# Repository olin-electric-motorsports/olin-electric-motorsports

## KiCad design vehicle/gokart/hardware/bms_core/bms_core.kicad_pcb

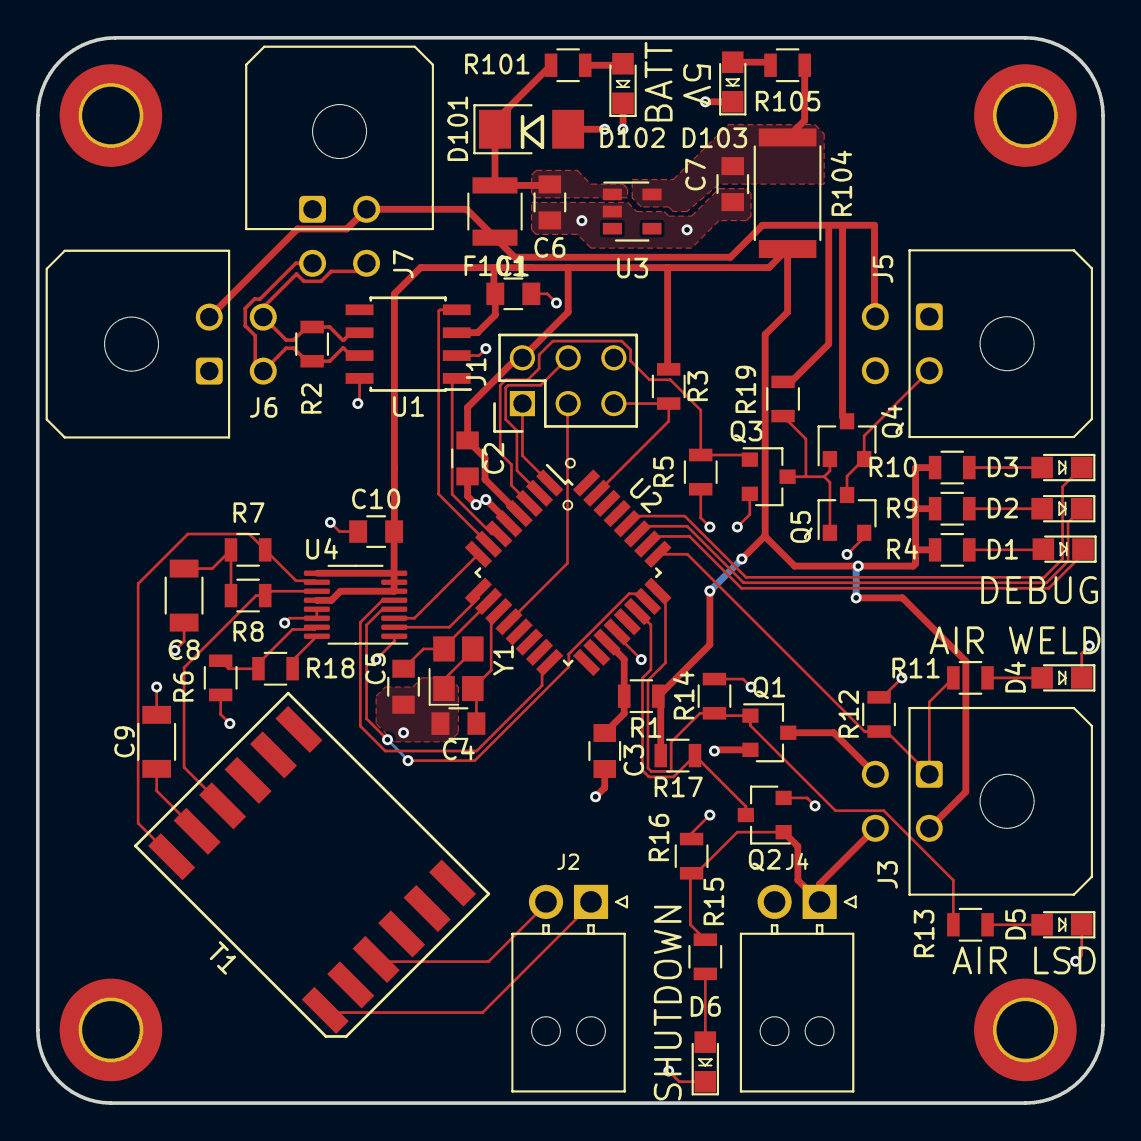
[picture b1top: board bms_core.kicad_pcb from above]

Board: 2 copper layers, 59.2 x 59.2 mm, 60 parts (0 on the bottom side), 47 nets.

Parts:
C1, C2: C_0.1uF; C_0805_OEM
C3: C_100pF; C_0805_OEM
C4, C5: C_30pF; C_0805_OEM
C6, C7, C10: C_1uF; C_0805_OEM
C8, C9: C_10nF; C_1206_OEM
D1, D2, D3, D4, D5, D6, D102, D103: LED_0805; LED_0805_OEM
D101: D_Zener_18V; DO-214AA
F101: F_500mA_16V; Fuse_1210
J1: CONN_02X03; Pin_Header_Straight_2x03
J2, J4: NanoFit_RA_TH_02; NanoFit_Molex_1x02x2.50mm_Angled_OEM
J3, J5, J6, J7: MicroFit_RA_4
Q1, Q2, Q3, Q5: SSM3K333R; SOT-23F
Q4: SSM3J334R; SOT-23F
R1: R_100; R_0805_OEM
R2: R_120_DNP; R_0805_OEM
R3, R5, R12, R14, R16, R17: R_10K; R_0805_OEM
R4, R9, R10, R11, R13, R15, R105: R_200; R_0805_OEM
R6, R18, R19, R101: R_1K; R_0805_OEM
R7, R8: R_60.4; R_0805_OEM
R104: R_0_2512; R_2512_OEM
T1: T_LAN_SM91501ALE
U1: MCP2561-E_SN; SOIC-8_3.9x4.9mm_Pitch1.27mm_OEM
U2: ATMEGA16M1; TQFP-32_7x7mm_Pitch0.8mm
U3: AP7370; SOT-23-5
U4: LTC6820HMS; MSOP-16_3x4mm_P0.5mm
Y1: Crystal_SMD; Crystal_SMD_FA238

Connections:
+5V: C1.1, C2.1, C10.1, J1.2, J3.2, R1.1, R3.1, R4.1, R9.1, R10.1, R17.2, R104.1, U1.3, U2.4, U4.6, U4.7, U4.8, U4.9, U4.12
+BATT: F101.2, J5.3, J6.2, J7.2, Q4.3, R19.1
/AIR_LSD: Q1.1, R13.1, R14.1, U2.24
/AIR_WELD: J3.1, R11.1, R12.1, U2.25
/CAN_+: J6.3, J7.3, R2.1, U1.7
/CAN_-: J6.4, J7.4, R2.2, U1.6
/CAN_RX: U1.4, U2.7
/CAN_TX: U1.1, U2.6
/COIL_+: J3.4, J4.1, Q2.1, R15.1, R16.1
/COIL_-: J3.3, Q1.3
/CS_iso: U2.16, U4.5
/DEBUG_1: D1.1, U2.26
/DEBUG_2: D2.1, U2.27
/DEBUG_3: D3.1, U2.28
/FAN_PWM: J5.2, Q4.2, Q5.3
/FAN_PWM_RAW: Q3.1, R5.1, U2.3
/MISO: J1.1, U2.1
/MISO_iso: U2.8, U4.3
/MOSI: J1.4, U2.2
/MOSI_iso: U2.9, U4.2
/RESET: J1.5, R3.2, U2.31
/SCK: J1.3, U2.12
/SCK_iso: U2.23, U4.4
/SHUTDOWN_SENSE: Q2.3, R17.1, U2.22
GND: C1.2, C2.2, C3.2, C4.2, C5.2, C6.2, C7.2, C8.2, C9.2, C10.2, D4.1, D5.1, D6.1, D101.2, D102.1, D103.1, J1.6, J4.2, J5.1, J6.1, J7.1, Q1.2, Q2.2, Q3.2, Q5.2, R5.2, R6.2, R12.2, R14.2, R16.2, U1.2, U1.8, U2.5, U2.20, U3.2, U4.1, U4.13, U4.14, Y1.2, Y1.4
unnamed: C3.1, R1.2, U2.19
unnamed: C4.1, U2.11, Y1.1
unnamed: C5.1, U2.10, Y1.3
unnamed: C6.1, D101.1, F101.1, R101.1, U3.1
unnamed: C7.1, R104.2, R105.1, U3.5
unnamed: C8.1, R7.2, R8.1
unnamed: C9.1, T1.11
unnamed: D1.2, R4.2
unnamed: D2.2, R9.2
unnamed: D3.2, R10.2
unnamed: D4.2, R11.2
unnamed: D5.2, R13.2
unnamed: D6.2, R15.2
unnamed: D102.2, R101.2
unnamed: D103.2, R105.2
unnamed: J2.1, T1.1
unnamed: J2.2, T1.3
unnamed: Q3.3, Q4.1, Q5.1, R19.2
unnamed: R7.1, T1.12, U4.10
unnamed: R8.2, T1.10, U4.11
unnamed: R18.1, U4.16
unnamed: R6.1, R18.2, U4.15

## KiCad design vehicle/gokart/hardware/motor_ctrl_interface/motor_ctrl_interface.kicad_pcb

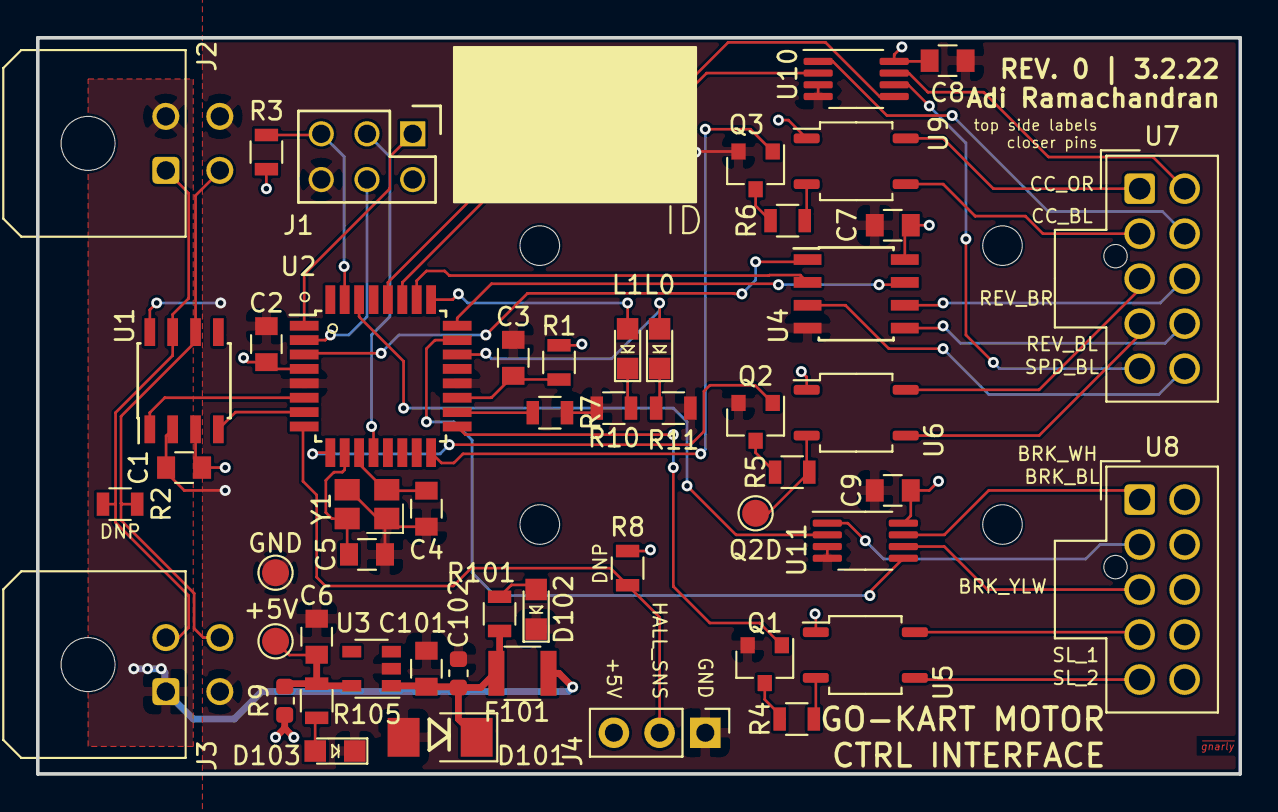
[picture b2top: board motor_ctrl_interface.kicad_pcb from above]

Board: 2 copper layers, 66.8 x 40.9 mm, 52 parts (0 on the bottom side), 55 nets.

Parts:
+5V: Test_Point_SMD; TestPoint_Pad_D1.5mm
C1, C2, C7, C8, C9, C101: C_0.1uF; C_0805_OEM
C3: C_100pF; C_0805_OEM
C4, C5: C_30pF; C_0805_OEM
C6: C_1uF; C_0805_OEM
C102: C_2.2uF; C_0603_1608Metric
D101: D_Zener_18V; DO-214AA
D102, D103: LED_0805; LED_0805_OEM
F101: F_500mA_16V; Fuse_1210
GND: Test_Point_SMD; TestPoint_Pad_D1.5mm
J1: CONN_02X03; Pin_Header_Straight_2x03
J2, J3: MicroFit_RA_4
J4: CONN_01X03; PinHeader_1x03_P2.54mm_Vertical
L0, L1: LED_0805; LED_0805_OEM
Q1, Q2, Q3: SSM3K333R; SOT-23F
Q2D: Test_Point_SMD; TestPoint_Pad_D1.5mm
R1: R_100; R_0805_OEM
R2: R_120_DNP; R_0805_OEM
R3, R7, R8: R_10K; R_0805_OEM
R4, R5, R6, R101: R_1K; R_0805_OEM
R9: R_0; R_0603_1608Metric
R10, R11: R_499; R_0805_OEM
R105: R_200; R_0805_OEM
U1: MCP2561-E_SN; SOIC-8_3.9x4.9mm_Pitch1.27mm_OEM
U2: ATMEGA16M1; TQFP-32_7x7mm_Pitch0.8mm
U3: AP7370; SOT-23-5
U4: AD5220BRZ50; SOIC-8_3.9x4.9mm_Pitch1.27mm_OEM
U5, U6, U9: CPC1004N; SOP-4_3.8x4.1mm_P2.54mm
U7, U8: NanoFit_VT_TH_10; NanoFit_VT_10
U10, U11: SN74LVC2G53; MSOP-8_3x3mm_P0.65mm
Y1: Crystal_SMD; Crystal_SMD_FA238

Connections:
+5V: C1.1, C2.1, C7.1, C8.1, C9.1, J1.2, J4.3, R1.1, R3.1, R8.1, R9.1, U1.3, U2.4, U4.8, U5.1, U6.1, U9.1, U10.8, U11.8
+BATT: F101.2, J2.2, J3.1
/BRK_A: U2.23, U11.5
/BRK_INH: U2.30, U11.2
/CAN_+: J2.1, J3.2, R2.1, U1.7
/CAN_-: J2.3, J3.4, R2.2, U1.6
/CAN_RX: U1.4, U2.7
/CAN_TX: U1.1, U2.6
/CONN_BRK_BLACK: U8.2, U11.1
/CONN_BRK_WHITE: U8.1, U11.7
/CONN_BRK_YELLOW: U8.3, U11.6
/CONN_CC_BLACK: U7.2, U9.3
/CONN_CC_ORANGE: U7.1, U9.4
/CONN_REVERSE_BLACK: U6.3, U7.4
/CONN_REVERSE_BROWN: U6.4, U7.3
/CONN_SL_1: U5.4, U8.4
/CONN_SL_2: U5.3, U8.5
/CONN_SPD_BLACK: U7.7, U10.1
/CONN_SPD_BLUE: U7.5, U10.6
/CONN_SPD_ORANGE: U7.6, U10.7
/CONN_THR_5V: U4.3, U7.10
/CONN_THR_GND: U4.6, U7.8
/CONN_THR_GREEN: U4.5, U7.9
/CRUISE_CONTROL: Q3.1, U2.16
/HALL_SNS: J4.2, R8.2, U2.8
/ID_PULLDOWN: R7.1, U2.18
/LED_0: L0.2, U2.22
/LED_1: L1.2, U2.25
/MISO: J1.1, U2.1
/MOSI: J1.4, U2.2
/POT_CLK: U2.3, U4.1
/POT_U~D: U2.26, U4.2
/POT_~CS: U2.24, U4.7
/RESET: J1.5, R3.2, U2.31
/REVERSE: Q2.1, U2.9
/SCK: J1.3, U2.12
/SL_MODE: Q1.1, U2.17
/SPD_A: U2.28, U10.5
/SPD_INH: U2.27, U10.2
GND: C1.2, C2.2, C3.2, C4.2, C5.2, C6.2, C7.2, C8.2, C9.2, C101.2, C102.2, D101.2, D102.1, D103.1, GND.1, J1.6, J2.4, J3.3, J4.1, Q1.2, Q2.2, Q3.2, R7.2, R10.2, R11.2, U1.2, U1.8, U2.5, U2.20, U3.2, U4.4, U10.3, U10.4, U11.3, U11.4, Y1.2, Y1.4
unnamed: C3.1, R1.2, U2.19
unnamed: C4.1, U2.11, Y1.1
unnamed: C5.1, U2.10, Y1.3
unnamed: +5V.1, C6.1, R9.2, R105.1, U3.5
unnamed: C101.1, C102.1, D101.1, F101.1, R101.1, U3.1
unnamed: L1.1, R10.1
unnamed: L0.1, R11.1
unnamed: D102.2, R101.2
unnamed: D103.2, R105.2
unnamed: Q1.3, R4.2
unnamed: Q2.3, R5.2
unnamed: Q3.3, R6.2
unnamed: R4.1, U5.2
unnamed: Q2D.1, R5.1, U6.2
unnamed: R6.1, U9.2

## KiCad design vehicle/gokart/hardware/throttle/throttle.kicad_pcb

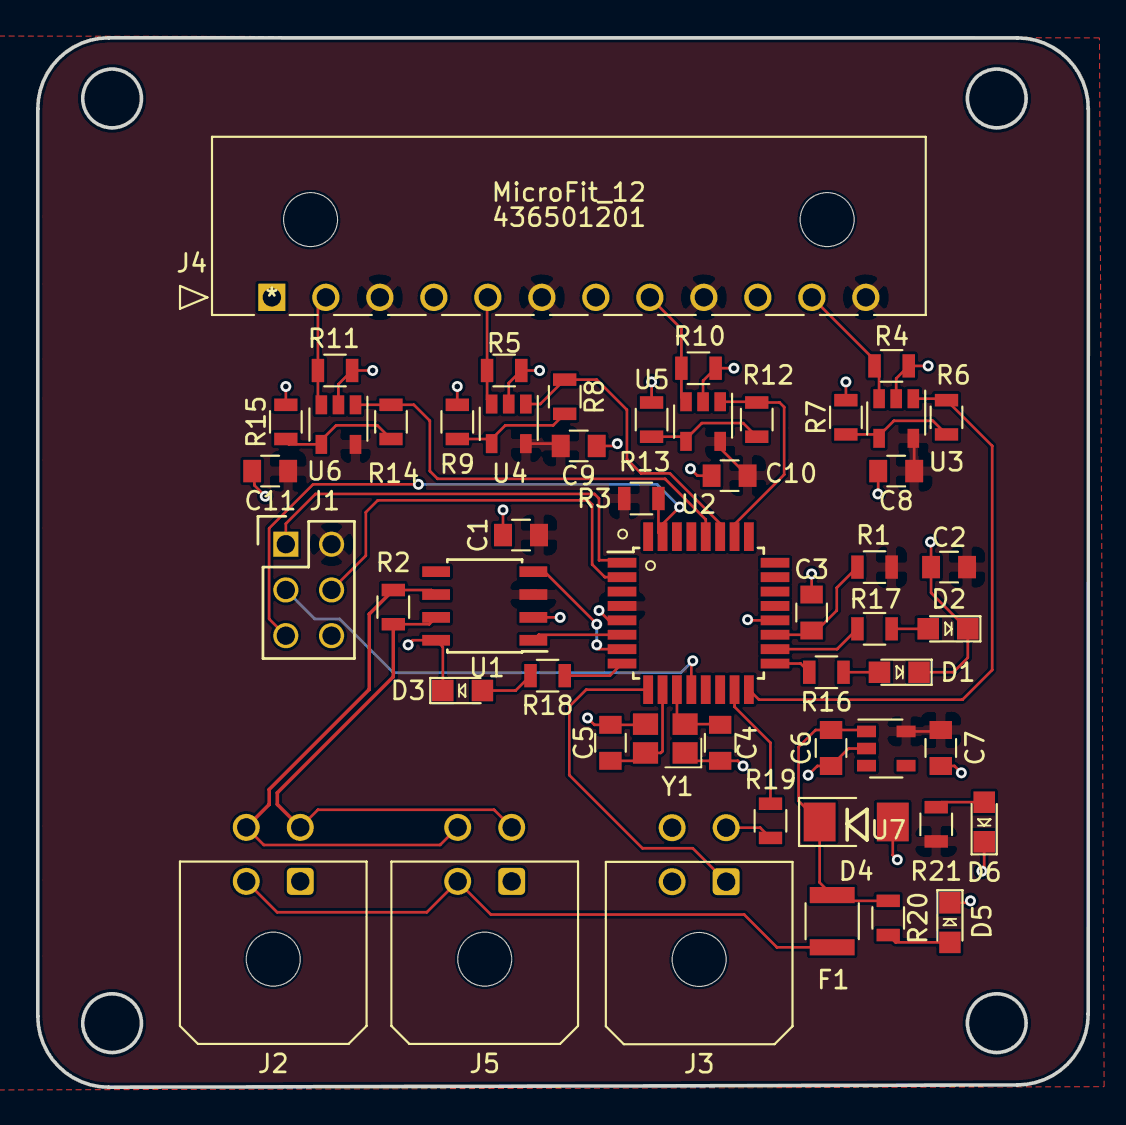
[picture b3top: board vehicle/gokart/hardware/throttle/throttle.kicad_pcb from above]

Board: 2 copper layers, 58.4 x 58.3 mm, 52 parts (0 on the bottom side), 38 nets.

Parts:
C1, C2: C_0.1uF; C_0805_OEM
C3: C_100pF; C_0805_OEM
C4, C5: C_30pF; C_0805_OEM
C6, C7, C8, C9, C10, C11: C_1uF; C_0805_OEM
D1, D5, D6: LED_0805; LED_0805_OEM
D2: LED_0805_Amber; LED_0805_OEM
D3: LED_0805_Red; LED_0805_OEM
D4: D_Zener_18V; DO-214AA
F1: F_500mA_16V; Fuse_1210
J1: CONN_02X03; Pin_Header_Straight_2x03
J2, J3, J5: MicroFit_RA_4
J4: MicroFit_12; MicroFit12_ra
R1: R_100; R_0805_OEM
R2: R_120_DNP; R_0805_OEM
R3, R6, R8, R12, R14: R_10K; R_0805_OEM
R4, R5, R10, R11: R_100K; R_0805_OEM
R7, R9, R13, R15: R_10K_DNP; R_0805_OEM
R16, R17, R18, R19, R21: R_200; R_0805_OEM
R20: R_1K; R_0805_OEM
U1: MCP2561-E_SN; SOIC-8_3.9x4.9mm_Pitch1.27mm_OEM
U2: ATMEGA16M1; TQFP-32_7x7mm_Pitch0.8mm
U3, U4, U5, U6: MCP6001; SOT-23-5_OEM
U7: AP7370; SOT-23-5
Y1: Crystal_SMD; Crystal_SMD_FA238

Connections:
+5V: C1.1, C2.1, C7.1, C8.2, C9.2, C10.2, C11.2, J1.2, J4.3, J4.6, J4.9, J4.12, R1.1, R3.1, R21.1, U1.3, U2.4, U3.5, U4.5, U5.5, U6.5, U7.5
+BATT: F1.2, J2.2, J5.2
/CAN_+: J2.3, J5.3, R2.1, U1.7
/CAN_-: J2.4, J5.4, R2.2, U1.6
/CAN_RX: U1.4, U2.7
/CAN_TX: U1.1, U2.6
/MISO: J1.1, U2.1
/MOSI: J1.4, U2.2
/PROGRAMMINGLED1: R16.1, U2.17
/PROGRAMMINGLED2: R17.1, U2.18
/PROGRAMMINGLED3: R18.1, U2.8
/READY_TO_DRIVE_LED: R19.1, U2.15
/RESET: J1.5, R3.2, U2.31
/SCK: J1.3, U2.12
/START_BUTTON: J3.1, U2.9
/VIN1: J4.11, R4.2, U3.3
/VIN2: J4.8, R10.2, U5.3
/VIN3: J4.5, R5.2, U4.3
/VIN4: J4.2, R11.2, U6.3
/VOUT1: R6.1, U2.16, U3.1
/VOUT2: R12.1, U2.26, U5.1
/VOUT3: R8.1, U2.27, U4.1
/VOUT4: R14.1, U2.28, U6.1
GND: C1.2, C2.2, C3.2, C4.2, C5.2, C6.2, C7.2, C8.1, C9.1, C10.1, C11.1, D1.1, D2.1, D3.1, D4.2, D5.1, D6.1, J1.6, J2.1, J3.2, J3.4, J4.1, J4.4, J4.7, J4.10, J5.1, R4.1, R5.1, R7.2, R9.2, R10.1, R11.1, R13.2, R15.2, U1.2, U1.8, U2.5, U2.20, U3.2, U4.2, U5.2, U6.2, U7.2, Y1.2, Y1.4
unnamed: C3.1, R1.2, U2.19
unnamed: C4.1, U2.11, Y1.1
unnamed: C5.1, U2.10, Y1.3
unnamed: C6.1, D4.1, F1.1, R20.1, U7.1
unnamed: D1.2, R16.2
unnamed: D2.2, R17.2
unnamed: D3.2, R18.2
unnamed: D5.2, R20.2
unnamed: D6.2, R21.2
unnamed: J3.3, R19.2
unnamed: R6.2, R7.1, U3.4
unnamed: R8.2, R9.1, U4.4
unnamed: R12.2, R13.1, U5.4
unnamed: R14.2, R15.1, U6.4

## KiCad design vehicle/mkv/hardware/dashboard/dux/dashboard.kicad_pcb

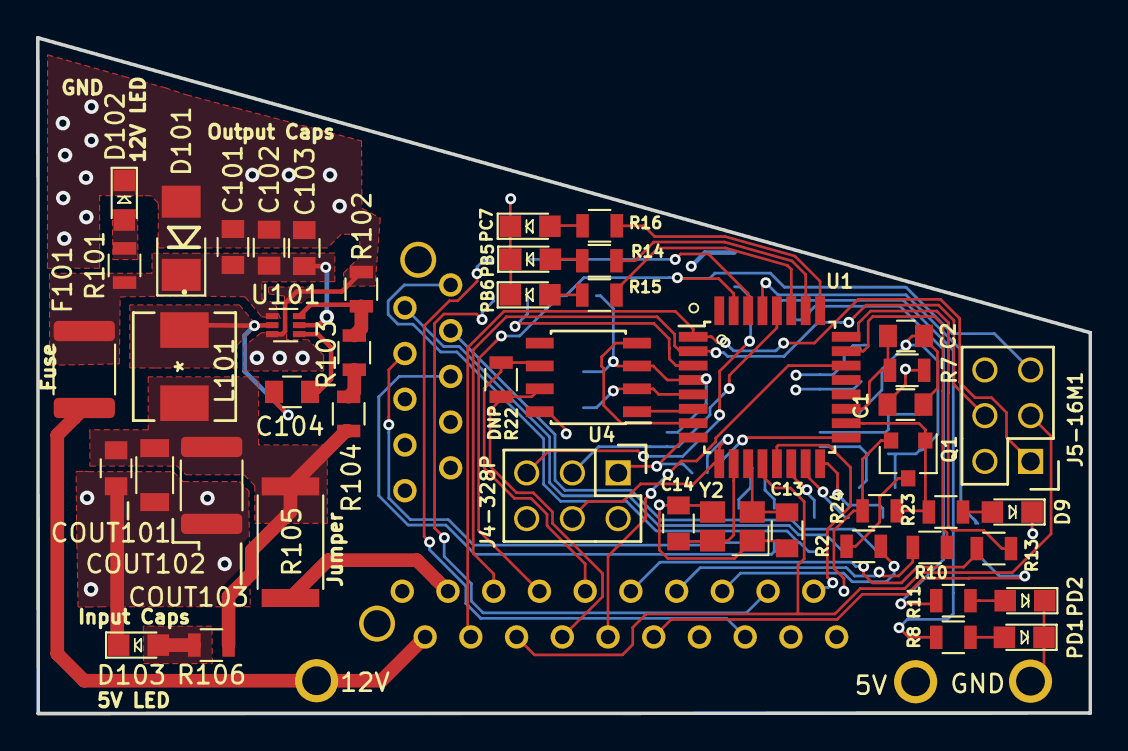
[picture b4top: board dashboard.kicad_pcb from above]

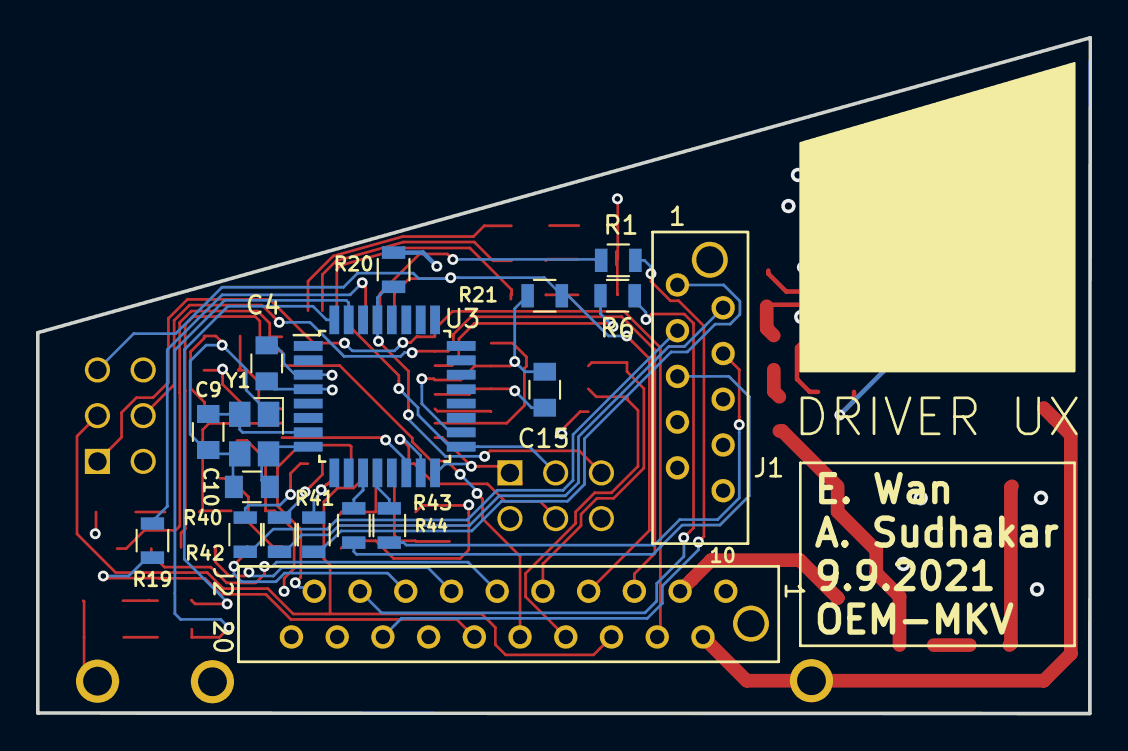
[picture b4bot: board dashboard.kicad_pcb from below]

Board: 4 copper layers, 58.5 x 37.5 mm, 68 parts (18 on the bottom side), 65 nets.

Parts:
C1, C4, C15, C101, C104: C_0.1uF; C_0805_OEM
C2: C_100pF; C_0805_OEM
C9, C10, C13, C14: C_30pF; C_0805_OEM
C102, C103: C_10uF_25V; C_0805_OEM
COUT101: C_10uF; C_0805_OEM
COUT102: C_22uF; C_1206_OEM
COUT103: C_33uF; C_1812_4532Metric
D3, D4, D5, D6, D8, D9: LED; LED_0805_OEM
D101: D_Zener_18V; DO-214AA
D102, D103: LED_0805; LED_0805_OEM
F101: F_2.6A_16V; Fuse_1812_4532Metric
J1: MM_F_VT_10; micromatch_female_vert_10
J2: MM_F_VT_20; micromatch_female_vert_20
J4-328P, J5-16M1: CONN_02X03; Pin_Header_Straight_2x03
L101: L_4.7uH; IHLP2020BZER4R7M11-L_4.7_3.2A
Q1: SSM3K333R; SOT-23F
R1, R6, R8, R10, R11, R13, R14, R15, R16, R19, R23, R40, R41, R42, R106: R_200; R_0805_OEM
R2, R7: R_100; R_0805_OEM
R20, R102: R_10K; R_0805_OEM
R21: R_10k; R_0805_OEM
R22: R_120; R_0805_OEM
R24: R_100k; R_0805_OEM
R43, R44: R_475; R_0805_OEM
R101: R_1K; R_0805_OEM
R103: R_51.1K; R_0805_OEM
R104: R_22K; R_0805_OEM
R105: R_0_2512; R_2512_OEM
TP1: TP_12V; tp_1.6mm
TP3: TP_5V; tp_1.6mm
TP5: TP_GND; tp_1.6mm
U1: ATMEGA16M1; TQFP-32_7x7mm_Pitch0.8mm
U3: ATmega328P-AU; TQFP-32_7x7mm_P0.8mm
U4: CAN_Transceiver; SOIC-8_3.9x4.9mm_Pitch1.27mm_OEM
U101: TPS563231; SOT-563
Y1, Y2: Crystal_SMD; Crystal_SMD_FA238

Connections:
+5V: C1.1, C4.1, C15.1, J1.6, J2.3, J2.18, J4-328P.2, J5-16M1.2, R7.1, R20.1, R21.1, R105.1, TP3.1, U1.4, U3.4, U3.18, U4.3
+12V: F101.1, J2.2, TP1.1
/BMS_LED: J2.12, R19.2
/BRAKE_LED: J1.3, R40.1
/CANH: J2.8, R22.1, U4.7
/CANL: J2.9, R22.2, U4.6
/CS: U1.17, U3.14
/HV_LED: J1.2, R42.1
/IMD_LED: J2.13, R10.1
/LV_LED: J1.1, R41.1
/PM_MISO: J2.4, J5-16M1.1, U1.1
/PM_MOSI: J2.5, J5-16M1.4, U1.2
/PM_RESET: J2.7, J5-16M1.5, R21.2, U1.31
/PM_SCK: J2.6, J5-16M1.3, U1.12
/RJLED1: J2.16, R1.1
/RJLED2: J2.17, R6.1
/RTD_LSD: J2.15, R2.1
/RXCAN: U1.7, U4.4
/SM_MISO: J4-328P.1, U1.8, U3.16
/SM_MOSI: J4-328P.4, U1.9, U3.15
/SM_RESET: J4-328P.5, R20.2, U3.29
/SM_SCK: J4-328P.3, U1.28, U3.17
/SOC_LED_BAR: J1.5, R44.1
/SPEED_LED_BAR: J1.4, R43.1
/START_BTN: J2.10, U1.22
/START_LED: J2.11, R13.1
/STR_POT_SENSE: J2.19, U1.13
/TXCAN: U1.6, U4.1
/XTAL1: C9.1, U3.7, Y1.1
/XTAL2: C10.1, U3.8, Y1.3
GND: C1.2, C2.2, C4.2, C9.2, C10.2, C13.2, C14.2, C15.2, C101.2, C102.2, C103.2, COUT101.2, COUT102.1, COUT103.2, D3.1, D4.1, D5.1, D6.1, D8.1, D9.1, D101.2, D102.1, D103.1, J1.7, J1.8, J1.9, J1.10, J2.1, J2.14, J2.20, J4-328P.6, J5-16M1.6, Q1.2, R24.2, R102.2, TP5.1, U1.5, U3.3, U4.2, U4.8, U101.3, Y1.2, Y1.4, Y2.2, Y2.4
unnamed: C2.1, R7.2, U1.19
unnamed: C13.1, U1.11, Y2.1
unnamed: C14.1, U1.10, Y2.3
unnamed: C101.1, C102.1, C103.1, D101.1, F101.2, R101.1, U101.1, U101.5
unnamed: C104.1, L101.1, U101.2
unnamed: C104.2, U101.4
unnamed: COUT101.1, COUT102.2, COUT103.1, L101.2, R104.1, R105.2, R106.1
unnamed: D3.2, R8.1
unnamed: D4.2, R11.1
unnamed: D5.2, R14.2
unnamed: D6.2, R15.2
unnamed: D8.2, R16.2
unnamed: D9.2, R23.2
unnamed: D102.2, R101.2
unnamed: D103.2, R106.2
unnamed: Q1.1, R23.1, R24.1, U1.18
unnamed: Q1.3, R2.2
unnamed: R1.2, U1.30
unnamed: R6.2, U1.3
unnamed: R8.2, U3.31
unnamed: R10.2, U1.23
unnamed: R11.2, U3.32
unnamed: R13.2, U1.24
unnamed: R14.1, U1.26
unnamed: R15.1, U1.27
unnamed: R16.1, U1.25
unnamed: R19.1, U1.29
unnamed: R40.2, U1.16
unnamed: R41.2, U1.14
unnamed: R42.2, U1.15
unnamed: R43.2, U3.12
unnamed: R44.2, U3.11
unnamed: R102.1, R103.2, U101.6
unnamed: R103.1, R104.2

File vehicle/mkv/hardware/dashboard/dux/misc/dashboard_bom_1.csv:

Component,Description,Part,References,Value,Footprint,Quantity Per PCB,Datasheet,Package,MPN,MFN,PurchasingLink,Link,Digi-key Part Number,Purchasing Link
1,,C_0.1uF-formula,C1 C4 C15 C101 C103,C_0.1uF,C_0805_OEM,5,http://datasheets.avx.com/X7RDielectric.pdf,Value,478-3352-1-ND,DK,https://www.digikey.com/products/en?keywords=478-3352-1-ND,,,
2,,C_100pF-formula,C2,C_100pF,C_0805_OEM,1,https://katalog.we-online.de/pbs/datasheet/885012007057.pdf,Value,732-7852-1-ND,DK,https://www.digikey.com/product-detail/en/wurth-electronics-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,,,
3,,C_2.2uF-formula,C102,C_2.2uF,C_0603_1608Metric,1,http://www.yageo.com/documents/recent/UPY-GPHC_X5R_4V-to-50V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,,311-1451-1-ND,DK,https://www.digikey.com/product-detail/en/yageo/CC0603KRX5R6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,,,
4,,C_30pF-formula,C9 C10 C13 C14,C_30pF,C_0805_OEM,4,https://media.digikey.com/pdf/Data%20Sheets/Samsung%20PDFs/C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,Value,1276-1130-1-ND,DK,https://www.digikey.com/product-detail/en/samsung-electro-me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,,,
5,,C_22uF-formula,COUT101,C_22uF,C_1206_OEM,1,https://product.tdk.com/info/en/catalog/datasheets/mlcc_comm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,,445-11693-1-ND,DK,https://www.digikey.com/product-detail/en/tdk-corporation/C3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,,,
6,,C_33uF-formula,COUT102,C_33uF,C_1812_OEM,1,https://product.tdk.com/info/en/catalog/datasheets/mlcc_comm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,,445-3924-1-ND,C4532X7R1C336M250KC,https://www.digikey.com/product-detail/en/tdk-corporation/C4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,,,
7,,C_47uF-formula,COUT103,C_47uF,C_0805_OEM,1,http://www.samsungsem.com/kr/support/product-search/mlcc/__i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,,1276-6467-1-ND,DK,https://www.digikey.com/product-detail/en/samsung-electro-me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,,,
8,,D_Zener_18V-formula,D101,D_Zener_18V,DO-214AA,1,http://www.mccsemi.com/up_pdf/SMBJ5338B-SMBJ5388B(SMB).pdf,,SMBJ5355B-TPMSCT-ND,DK,https://www.digikey.com/products/en?keywords=SMBJ5355B-TPMSCT-ND,,,
9,Light emitting diode,LED,D3 D4 D5 D6 D8 D9,LED,LED_0805_OEM,6,,,,,,,,
10,,LED_0805-formula,D102 D103,LED_0805,LED_0805_OEM,2,http://www.osram-os.com/Graphics/XPic9/00078860_0.pdf,,475-1410-1-ND,DK,https://www.digikey.com/products/en?keywords=475-1410-1-ND,,,
11,,F_500mA_16V-formula,F101,F_500mA_16V,Fuse_1210,1,https://belfuse.com/resources/CircuitProtection/datasheets/0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,,507-1786-1-ND,DK,https://www.digikey.com/product-detail/en/bel-fuse-inc/0ZCH0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,,,
12,,CONN_02X03-formula,J4 J5,CONN_02X03,Pin_Header_Straight_2x03,2,http://portal.fciconnect.com/Comergent//fci/drawing/67996.pdf,Value,609-3234-ND,DK,https://www.digikey.com/product-detail/en/amphenol-fci/67997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,,,
13,,MM_F_VT_04-formula,J3,MM_F_VT_04,micromatch_female_vert_4,1,http://www.te.com/commerce/DocumentDelivery/DDEController?Ac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,,338068-4,TE,http://www.te.com/global-en/product-338068-4.html,,,
14,,MM_F_VT_10-formula,J1,MM_F_VT_10,micromatch_female_vert_10,1,http://www.te.com/commerce/DocumentDelivery/DDEController?Ac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,,1-338068-0,TE,http://www.te.com/global-en/product-1-338068-0.html,,,
15,,MM_F_VT_20-formula,J2,MM_F_VT_20,micromatch_female_vert_20,1,http://www.te.com/commerce/DocumentDelivery/DDEController?Ac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,,2-338068-0,TE,http://www.te.com/global-en/product-2-338068-0.html,,,
16,,L_100uH-formula,L101,L_100uH,L_100uH,1,https://product.tdk.com/info/en/catalog/datasheets/inductor_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,,445-15759-1-ND,Digikey,,https://www.digikey.com/product-detail/en/tdk-corporation/NL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,,
17,,SSM3K333R-formula,Q1,SSM3K333R,SOT-23F,1,https://drive.google.com/drive/folders/0B-V-iZf33Y4GNzhDQTJZanJRbVk,,SSM3K333RLFCT-ND,DK,https://www.digikey.com/product-detail/en/toshiba-semiconduc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,,,
18,,R_0_2512-formula,R104,R_0_2512,R_2512_OEM,1,http://www.te.com/commerce/DocumentDelivery/DDEController?Ac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,,A121322CT-ND,DK,https://www.digikey.com/products/en?keywords=A121322CT-ND,,,
19,,R_100-formula,R7,R_100,R_0805_OEM,1,https://www.seielect.com/Catalog/SEI-rncp.pdf,Value,RNCP0805FTD100RCT-ND,DK,https://www.digikey.com/products/en?keywords=RNCP0805FTD100RCT-ND,,,
20,,R_100K-formula,R103,R_100K,R_0805_OEM,1,https://industrial.panasonic.com/cdbs/www-data/pdf/RDA0000/A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,,P100KCCT-ND,DK,https://www.digikey.com/product-detail/en/panasonic-electron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,,,
21,Resistor,R,R24,R_100k,R_0805_OEM,1,~,,,,,,,
22,,R_10K-formula,R20 R21,R_10K,R_0805_OEM,2,http://www.bourns.com/data/global/pdfs/CRS.pdf,Value,CRS0805-FX-1002ELFCT-ND,DK,https://www.digikey.com/products/en?keywords=CRS0805-FX-1002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,,,
23,,R_200-formula,R22,R_120,R_0805_OEM,1,https://www.seielect.com/Catalog/SEI-RMCF_RMCP.pdf,Value,RMCF0805JT200RCT-ND,DK,https://www.digikey.com/products/en?keywords=RMCF0805JT200RCT-ND,,,
24,,R_200-formula,R1 R6 R8 R10 R11 R13 R14 R15 R16 R19 R40 R41 R42 R101 R105,R_200,R_0805_OEM,15,https://www.seielect.com/Catalog/SEI-RMCF_RMCP.pdf,,RMCF0805JT200RCT-ND,DK,https://www.digikey.com/products/en?keywords=RMCF0805JT200RCT-ND,,,
25,Resistor,R,R23,R_200,R_0805_OEM,1,~,,,,,,,
26,,R_25K-formula,R102,R_25K,R_0805_OEM,1,https://www.te.com/commerce/DocumentDelivery/DDEController?A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,,,A124124CT-ND,https://www.digikey.com/product-detail/en/te-connectivity-pa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,,CPF-A-0805B25KE,
27,,R_475-formula,R43 R44,R_475,R_0805_OEM,2,http://www.yageo.com.tw/exep/pages/download/literatures/PYu-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,,311-475CRCT-ND,DK,https://www.digikey.com/products/en?keywords=311-475CRCT-ND,,,
28,,ATMEGA16M1-formula,U1,ATMEGA16M1,TQFP-32_7x7mm_Pitch0.8mm,1,http://ww1.microchip.com/downloads/en/DeviceDoc/Atmel-8209-8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,,ATMEGA16M1-AU-ND,DK,https://www.digikey.com/product-detail/en/atmel/ATMEGA16M1-A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,,,
29,,ATmega328-AU-formula,U3,ATmega328P-AU,TQFP-32_7x7mm_P0.8mm,1,http://ww1.microchip.com/downloads/en/DeviceDoc/Atmel-8025-8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,,,,,,,
30,,MCP2561-E_SN-formula,U4,CAN_Transceiver,SOIC-8_3.9x4.9mm_Pitch1.27mm_OEM,1,http://www.microchip.com/mymicrochip/filehandler.aspx?ddocna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,Value,MCP2561-E/SN-ND,DK,https://www.digikey.com/products/en?keywords=mcp2561-e%2Fsn,,,
31,,TPS560430YF-formula,U101,TPS560430YF,SOT-23-6_Handsoldering,1,http://www.ti.com/lit/ds/symlink/tps560430.pdf,,TPS560430YFDBVR,TPS560430YFDBVR-ND,,,,https://www.digikey.com/product-detail/en/texas-instruments/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
32,,Crystal_SMD-formula,Y1 Y2,Crystal_SMD,Crystal_SMD_FA238,2,http://www.txccorp.com/download/products/quartz_crystals/201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,Value,887-1125-1-ND,DK,https://www.digikey.com/product-detail/en/txc-corporation/7M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,,,





Component Groups:,32
Component Count:,63
Fitted Components:,63
Number of PCBs:,1
Total components:,63
Schematic Version:,1
Schematic Date:,2019-10-31
PCB Variant:,default
BoM Date:,Wed 12 Feb 2020 05:01:07 PM EST
Schematic Source:,/home/emilywan188/Documents/Formula/MKV-Boards/Boards/Driver_UX/dashboard_MKV_ewan.sch
KiCad Version:,Eeschema 5.1.4-e60b266~84~ubuntu18.04.1

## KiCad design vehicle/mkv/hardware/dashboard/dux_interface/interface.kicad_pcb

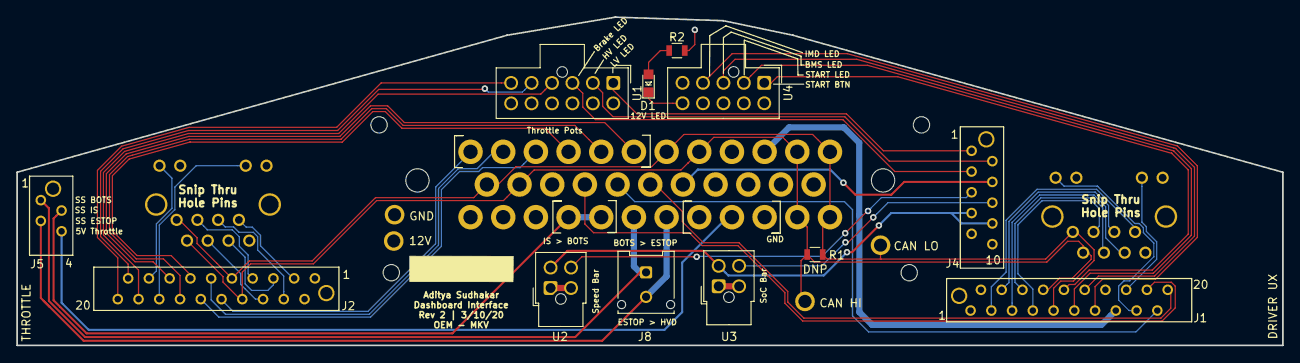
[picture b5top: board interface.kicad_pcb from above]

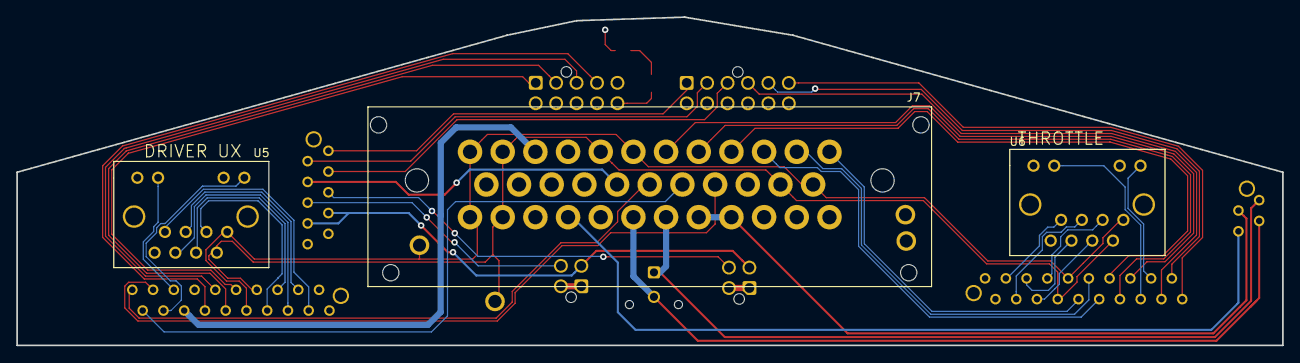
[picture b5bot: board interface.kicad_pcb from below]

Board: 4 copper layers, 154.9 x 40.2 mm, 19 parts (3 on the bottom side), 47 nets.

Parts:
12V: TestPoint; tp_1.6mm
CAN HI: TestPoint; tp_1.6mm
CAN LO: TestPoint; tp_1.6mm
D1: LED_0805; LED_0805_OEM
GND: TestPoint; tp_1.6mm
J1, J2: MM_F_VT_20; micromatch_female_vert_20
J4: MM_F_VT_10; micromatch_female_vert_10
J5: MM_F_VT_04; micromatch_female_vert_4
J7: Ampseal_35_VT; Ampseal_35
J8: MicroFit_RA_V_2; Molex_Micro-Fit_3.0_43045-0212_2x01_P3.00mm_Vertical
R1: R_120_DNP; R_0805_OEM
R2: R_1K; R_0805_OEM
U1: Nanofit_12; NanoFit_VT_TH_12
U2, U3: Nanofit_4; Molex_Nano-Fit_105310-xx04_2x02_P2.50mm_Vertical
U4: Nanofit_10; NanoFit_VT_TH_10
U5, U6: RJ45_VT; RJ45-Vertical

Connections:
+12V: 12V.1, J1.2, J2.2, J7.2, J7.3, J7.21, J7.22, R2.2
/5V_CAN_LOGGER: J5.4, J7.9
/5V_DUX: J1.3, U5.7
/5V_LED_BARS: J4.7, J4.8, U2.3, U3.3
/5V_STEERING: J4.4, J7.19
/5V_THROTTLE: J2.3, U6.7
/BMS_LED: J1.12, U4.3
/BOTS>ESTOP: J5.1, J7.6, J8.1
/BRAKE_LED: J4.3, U1.3
/CAN+: CAN HI.1, J1.8, J2.8, J7.11, J7.14, J7.31, J7.34, R1.2, U5.2, U6.2
/CAN-: CAN LO.1, J1.9, J2.9, J7.12, J7.13, J7.30, J7.35, R1.1, U5.1, U6.1
/DRIVE_MODE_+: J2.18, U1.4
/DRIVE_MODE_-: J2.20, U1.6
/DRIVE_MODE_SENSE: J2.19, U1.5
/ESTOP>HVD: J5.3, J7.7, J8.2
/HV_LED: J4.2, U1.2
/IMD_LED: J1.13, U4.4
/IS>BOTS: J5.2, J7.4, J7.5
/LV_LED: J4.1, U1.1
/MISO_DUX: J1.4, U5.5
/MISO_THROTTLE: J2.4, U6.5
/MOSI_DUX: J1.5, U5.6
/MOSI_THROTTLE: J2.5, U6.6
/RESET_DUX: J1.7, U5.3
/RESET_THROTTLE: J2.7, U6.3
/RJ45_LED_G_DUX: J1.17, U5.12
/RJ45_LED_G_THROTTLE: J2.17, U6.12
/RJ45_LED_O_DUX: J1.16, U5.10
/RJ45_LED_O_THROTTLE: J2.16, U6.10
/RTD_LSD: J1.15, J7.33
/SCK_DUX: J1.6, U5.4
/SCK_THROTTLE: J2.6, U6.4
/SOC_LED_BAR: J4.6, U3.4
/SPEED_LED_BAR: J4.5, U2.4
/START_BTN: J1.10, U4.1
/START_LED: J1.11, U4.2
/STEERING_POT_+: J1.18, J7.16
/STEERING_POT_-: J1.20, J7.18
/STEERING_POT_SENSE: J1.19, J7.17
/THROTTLE_POT_1_+: J2.10, J7.24
/THROTTLE_POT_1_-: J2.12, J7.26
/THROTTLE_POT_1_SENSE: J2.11, J7.25
/THROTTLE_POT_2_+: J2.13, J7.27
/THROTTLE_POT_2_-: J2.15, J7.29
/THROTTLE_POT_2_SENSE: J2.14, J7.28
GND: D1.1, GND.1, J1.1, J1.14, J2.1, J4.9, J4.10, J7.1, J7.8, J7.10, J7.15, J7.20, J7.23, J7.32, U1.7, U1.8, U1.9, U1.10, U1.11, U1.12, U2.1, U2.2, U3.1, U3.2, U4.5, U4.6, U4.7, U4.8, U4.9, U4.10, U5.8, U5.9, U5.11, U5.13, U5.14, U6.8, U6.9, U6.11, U6.13, U6.14
unnamed: D1.2, R2.1

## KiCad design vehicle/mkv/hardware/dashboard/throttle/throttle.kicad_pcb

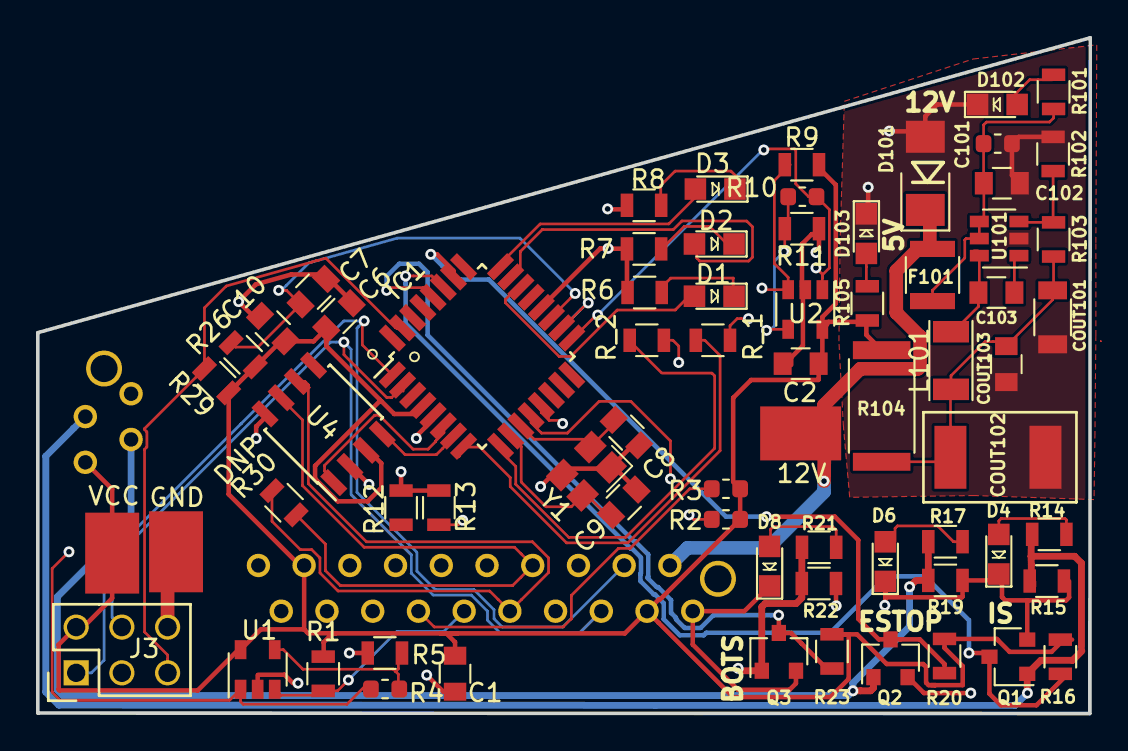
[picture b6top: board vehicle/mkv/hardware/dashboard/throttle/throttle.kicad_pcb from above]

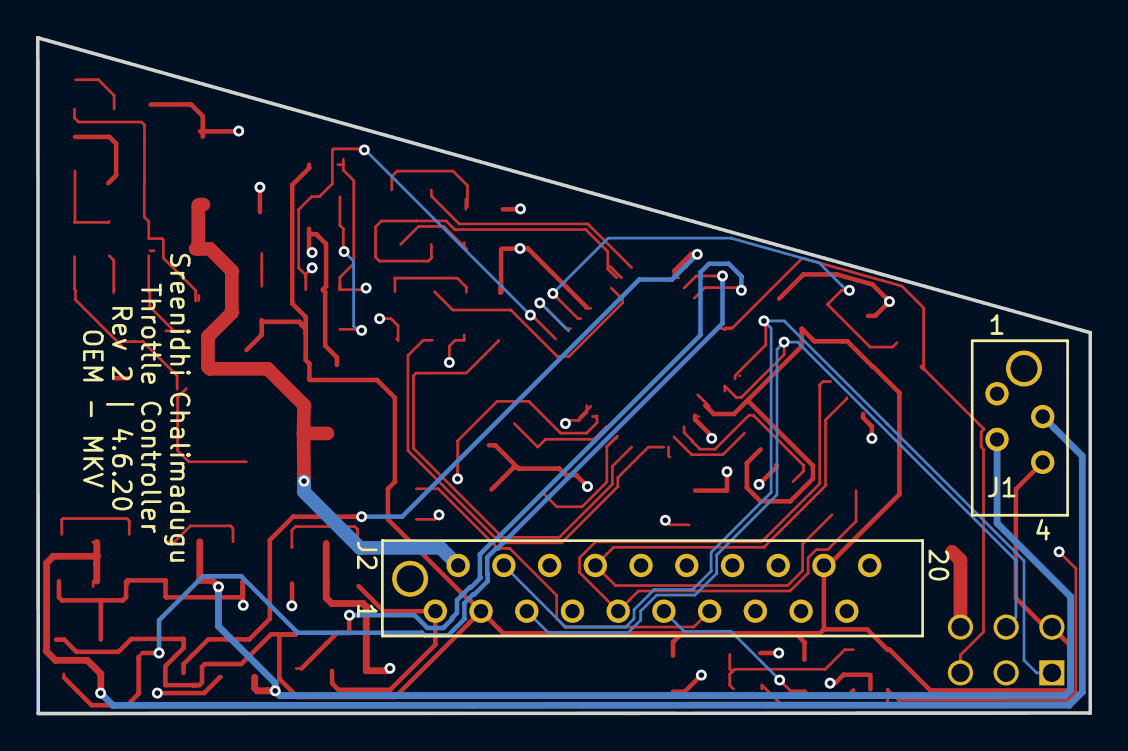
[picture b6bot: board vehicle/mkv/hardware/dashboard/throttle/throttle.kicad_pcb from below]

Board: 4 copper layers, 58.5 x 37.5 mm, 71 parts (2 on the bottom side), 47 nets.

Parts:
12V: TP; Test_Point_SMD
C1, C2, C6, C10, C103: C_0.1uF; C_0805_OEM
C7: C_100pF; C_0805_OEM
C8, C9: C_30pF; C_0805_OEM
C101: C_0.1uF; C_0603_1608Metric
C102: C_2.2uF; C_0805_OEM
COUT101: C_22uF; C_1206_OEM
COUT102: C_33uF; Fuse_1812
COUT103: C_47uF; C_0805_OEM
D1, D2, D3, D4, D6, D8, D102, D103: LED_0805; LED_0805_OEM
D101: D_Zener_18V; DO-214AA
F101: F_500mA_16V; Fuse_1210
GND: TP; Test_Point_SMD
IC1: ATMEGA16M1; TQFP-32_7x7mm_Pitch0.8mm
J1: micromatch_female_TOP_ENTRY_locking_4; micromatch_female_vert_4
J2: micromatch_female_TOP_ENTRY_locking_20; micromatch_female_vert_20
J3: CONN_02X03; Pin_Header_Straight_2x03
L101: L_100uH; L_100uH_OEM
Q1, Q2, Q3: SSM3K333R; SOT-23F
R1, R9: R_1M; R_0805_OEM
R2, R3, R4, R10: R_0; R_0603_1608Metric
R5, R11: R_2.2k; R_0805_OEM
R6, R7, R8, R101, R105: R_200; R_0805_OEM
R12, R13: R_22K; R_0805_OEM
R14, R17, R21: R_1k; R_0805_OEM
R15, R19, R22: R_100k; R_0805_OEM
R16, R20, R23, R29: R_10k; R_0805_OEM
R26: R_100; R_0805_OEM
R30: R_120 DNP; R_0805_OEM
R102: R_25K; R_0805_OEM
R103: R_100K; R_0805_OEM
R104: R_0_2512; R_2512_OEM
R_1, R_2: R_200; R_0805_OEM
U1, U2: MCP6001; SOT-23-5_OEM
U4: CAN_Transceiver; SOIC-8_3.9x4.9mm_Pitch1.27mm_OEM
U101: TPS560430YF; SOT-23-6_OEM
VCC: TP; Test_Point_SMD
Y1: Crystal_SMD; Crystal_SMD_FA238

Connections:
+12V: 12V.1, D101.1, F101.2, J2.2
/CANH: J2.8, R30.1, U4.7
/CANL: J2.9, R30.2, U4.6
/DRIVE_MODE_SENSE: IC1.13, J2.19, R13.1
/MISO: IC1.1, J2.4, J3.1
/MOSI: IC1.2, J2.5, J3.4
/PROGRAMMINGLED1: D1.2, IC1.22
/PROGRAMMINGLED2: D2.2, IC1.23
/PROGRAMMINGLED3: D3.2, IC1.24
/RESET: IC1.31, J2.7, J3.5, R29.2
/RXCAN: IC1.7, U4.4
/SCK: IC1.12, J2.6, J3.3
/SS_BOTS: J1.1, Q3.1, R21.1, R22.1
/SS_BOTS_OUT: IC1.28, Q3.3, R23.2
/SS_COCKPIT_ESTOP: J1.3, Q2.1, R17.1, R19.1
/SS_ESTOP_OUT: IC1.26, Q2.3, R20.2
/SS_INERTIA_OUT: IC1.27, Q1.3, R16.2
/SS_INERTIA_SWITCH: J1.2, Q1.1, R14.1, R15.1
/THROTTLE1SENSING: IC1.17, R10.1, U2.1
/THROTTLE1_RIGHT_SENSE: J2.11, R1.2, U1.3
/THROTTLE2SENSING: IC1.18, R4.1, U1.1
/THROTTLE2_LEFT_SENSE: J2.14, R9.2, U2.3
/TXCAN: IC1.6, U4.1
GND: C1.1, C2.1, C6.2, C7.2, C8.2, C9.2, C10.2, C101.2, C102.2, COUT101.2, COUT102.2, COUT103.2, D4.1, D6.1, D8.1, D101.2, D102.1, D103.1, GND.1, IC1.5, IC1.20, J2.1, J2.12, J2.15, J2.20, J3.6, Q1.2, Q2.2, Q3.2, R5.2, R6.2, R7.2, R8.2, R11.2, R12.1, R13.2, R15.2, R19.2, R22.2, R102.2, U1.2, U2.2, U4.2, U4.8, U101.2, Y1.2, Y1.4
unnamed: C7.1, IC1.19, R26.2
unnamed: C8.1, IC1.11, Y1.1
unnamed: C9.1, IC1.10, Y1.3
unnamed: C101.1, C102.1, F101.1, R101.1, U101.4, U101.5
unnamed: C103.1, L101.1, U101.6
unnamed: C103.2, U101.1
unnamed: COUT101.1, COUT102.1, COUT103.1, L101.2, R103.1, R104.1
unnamed: D1.1, R6.1
unnamed: D2.1, R7.1
unnamed: D3.1, R8.1
unnamed: D4.2, R14.2
unnamed: D6.2, R17.2
unnamed: D8.2, R21.2
unnamed: D102.2, R101.2
unnamed: D103.2, R105.2
unnamed: IC1.8, R_1.2
unnamed: IC1.9, R_2.2
unnamed: J2.10, R2.1
unnamed: J2.13, R3.2
unnamed: R4.2, R5.1, U1.4
unnamed: R10.2, R11.1, U2.4
unnamed: R102.1, R103.2, U101.3
VCC: C1.2, C2.2, C6.1, C10.1, IC1.4, J1.4, J2.3, J2.18, J3.2, R1.1, R2.2, R3.1, R9.1, R16.1, R20.1, R23.1, R26.1, R29.1, R104.2, R105.1, U1.5, U2.5, U4.3, VCC.1

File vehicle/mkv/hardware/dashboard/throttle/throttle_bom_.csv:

Component,References,Value,Footprint,Quantity Per PCB
1,C1 C2 C6 C10 C101 C103,C_0.1uF,C_0805_OEM,6
2,C7,C_100pF,C_0805_OEM,1
3,C102,C_2.2uF,C_0603_1608Metric,1
4,C8 C9,C_30pF,C_0805_OEM,2
5,COUT101,C_22uF,C_1206_OEM,1
6,COUT102,C_33uF,Fuse_1812,1
7,COUT103,C_47uF,C_0805_OEM,1
8,D101,D_Zener_18V,DO-214AA,1
9,D1 D2 D3 D4 D6 D8 D102 D103,LED_0805,LED_0805_OEM,8
10,F101,F_500mA_16V,Fuse_1210,1
11,IC1,ATMEGA16M1,TQFP-32_7x7mm_Pitch0.8mm,1
12,J3,CONN_02X03,Pin_Header_Straight_2x03,1
13,J2,micromatch_female_TOP_ENTRY_locking_20,micromatch_female_vert_20,1
14,J1,micromatch_female_TOP_ENTRY_locking_4,micromatch_female_vert_4,1
15,L101,L_100uH,L_100uH,1
16,Q1 Q2 Q3,SSM3K333R,SOT-23F,3
17,R2 R3,R_0,R_0603_1608Metric,2
18,R4 R10,R_0-formula,R_0603_1608Metric,2
19,R104,R_0_2512,R_2512_OEM,1
20,R26,R_100,R_0805_OEM,1
21,R15 R19 R22 R103,R_100k,R_0805_OEM,4
22,R16 R20 R23 R29,R_10k,R_0805_OEM,4
23,R30,R_120 DNP,R_0805_OEM,1
24,R1 R9,R_1M,R_0805_OEM,2
25,R14 R17 R21,R_1k,R_0805_OEM,3
26,R5 R11,R_2.2k,R_0805_OEM,2
27,R6 R7 R8 R101 R105 R_1 R_2,R_200,R_0805_OEM,7
28,R12 R13,R_22K,R_0805_OEM,2
29,R102,R_25K,R_0805_OEM,1
30,U4,CAN_Transceiver,SOIC-8_3.9x4.9mm_Pitch1.27mm_OEM,1
31,U1 U2,MCP6001,SOT-23-5_OEM,2
32,U101,TPS560430YF,SOT-23-6_OEM,1
33,Y1,Crystal_SMD,Crystal_SMD_FA238,1
,,,,
,,,,
,,,,
,,,,
,,,,
Component Groups:,,,,
Component Count:,,,,
Fitted Components:,,,,
Number of PCBs:,,,,
Total components:,,,,
Schematic Version:,,,,
Schematic Date:,,,,
PCB Variant:,,,,
BoM Date:,,,,
Schematic Source:,,,,
KiCad Version:,,,,

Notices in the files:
parts and their libraries:
Copyright 2021 Accelerated Designs. All rights reserved.
Copyright 2016 Accelerated Designs. All rights reserved.
